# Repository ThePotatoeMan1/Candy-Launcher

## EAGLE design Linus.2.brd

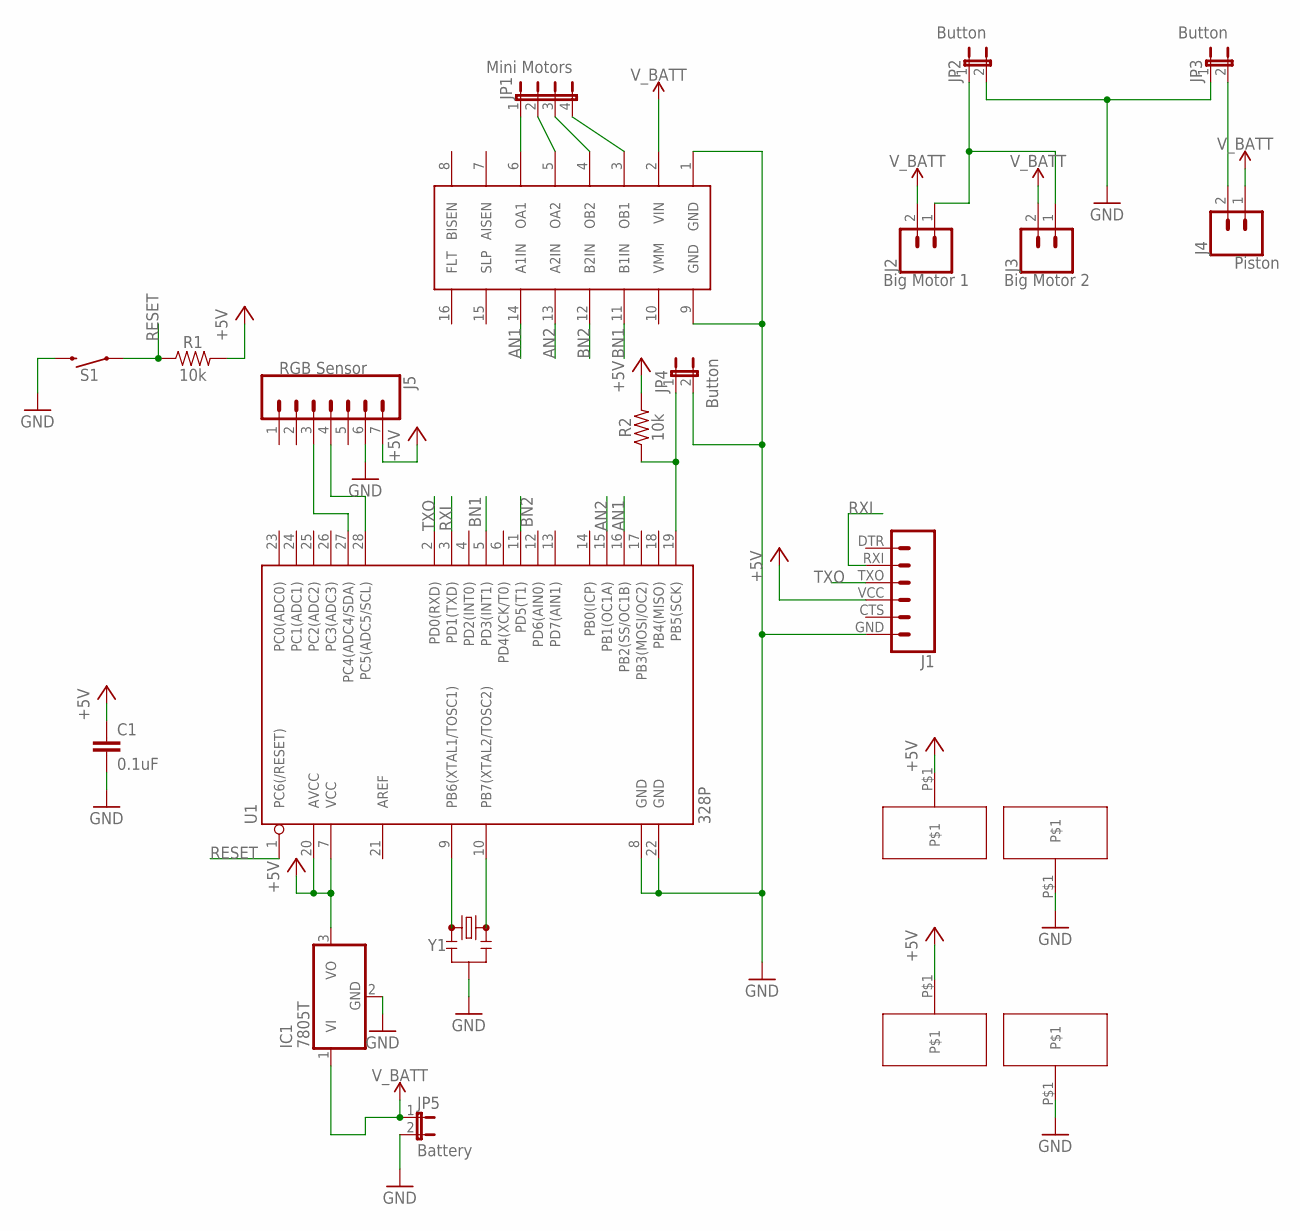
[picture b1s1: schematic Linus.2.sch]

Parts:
C1: 0.1uF; CAP-PTH-SMALL-KIT
IC1: 7805T; TO220H
J1: 6_PIN_SERIAL_CABLEPTH; FTDI_BASIC
J2: Big Motor 1; 1X02
J3: Big Motor 2; 1X02
J4: Piston; 1X02
J5: RGB Sensor; 1X07
JP1: Mini Motors; JP4
JP2, JP3, JP4: Button; JP1
JP5: Battery; JP1
R1, R2: 10k; AXIAL-0.3
S1: MOMENTARY-SWITCH-SPST-PTH-6.0MM; TACTILE_SWITCH_PTH_6.0MM
U1: 328P; DIP28
U$2: MOTOR_DRIVER
U$3, U$4, U$5, U$6: CONN_01
Y1: RESONATORPTH-7.6X3.8; RESONATOR-PTH-7.6X3.8

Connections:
+5V: C1.1, IC1.3 (VO), J1.VCC (4), J5.7, R1.P$2 (2), R2.P$2 (2), U1.7 (VCC), U1.20 (AVCC), U$3.P$1, U$5.P$1
AN1: U1.16 (PB2(SS/OC1B)), U$2.14 (A1IN)
AN2: U1.15 (PB1(OC1A)), U$2.13 (A2IN)
BN1: U1.5 (PD3(INT1)), U$2.11 (B1IN)
BN2: U1.11 (PD5(T1)), U$2.12 (B2IN)
GND: C1.2, IC1.2 (GND), J5.6, JP2.2, JP3.1, JP5.2, S1.3 (2), U$4.P$1, U$6.P$1, Y1.2
unnamed: J5.3, U1.27 (PC4(ADC4/SDA))
unnamed: J5.4, U1.28 (PC5(ADC5/SCL))
unnamed: U1.9 (PB6(XTAL1/TOSC1)), Y1.1
unnamed: U1.10 (PB7(XTAL2/TOSC2)), Y1.3
unnamed: JP1.1, U$2.6 (OA1)
unnamed: JP1.2, U$2.5 (OA2)
unnamed: JP1.3, U$2.4 (OB2)
unnamed: JP1.4, U$2.3 (OB1)
unnamed: J1.GND (6), JP4.2, U1.8 (GND), U1.22 (GND), U$2.1 (GND), U$2.9 (GND)
unnamed: J2.1, J3.1, JP2.1
unnamed: J4.2, JP3.2
unnamed: JP4.1, R2.P$1 (1), U1.19 (PB5(SCK))
RESET: R1.P$1 (1), S1.1, U1.1 (PC6(/RESET))
RXI: J1.RXI (2), U1.3 (PD1(TXD))
TXO: J1.TXO (3), U1.2 (PD0(RXD))
V_BATT: IC1.1 (VI), J2.2, J3.2, J4.1, JP5.1, U$2.2 (VIN)

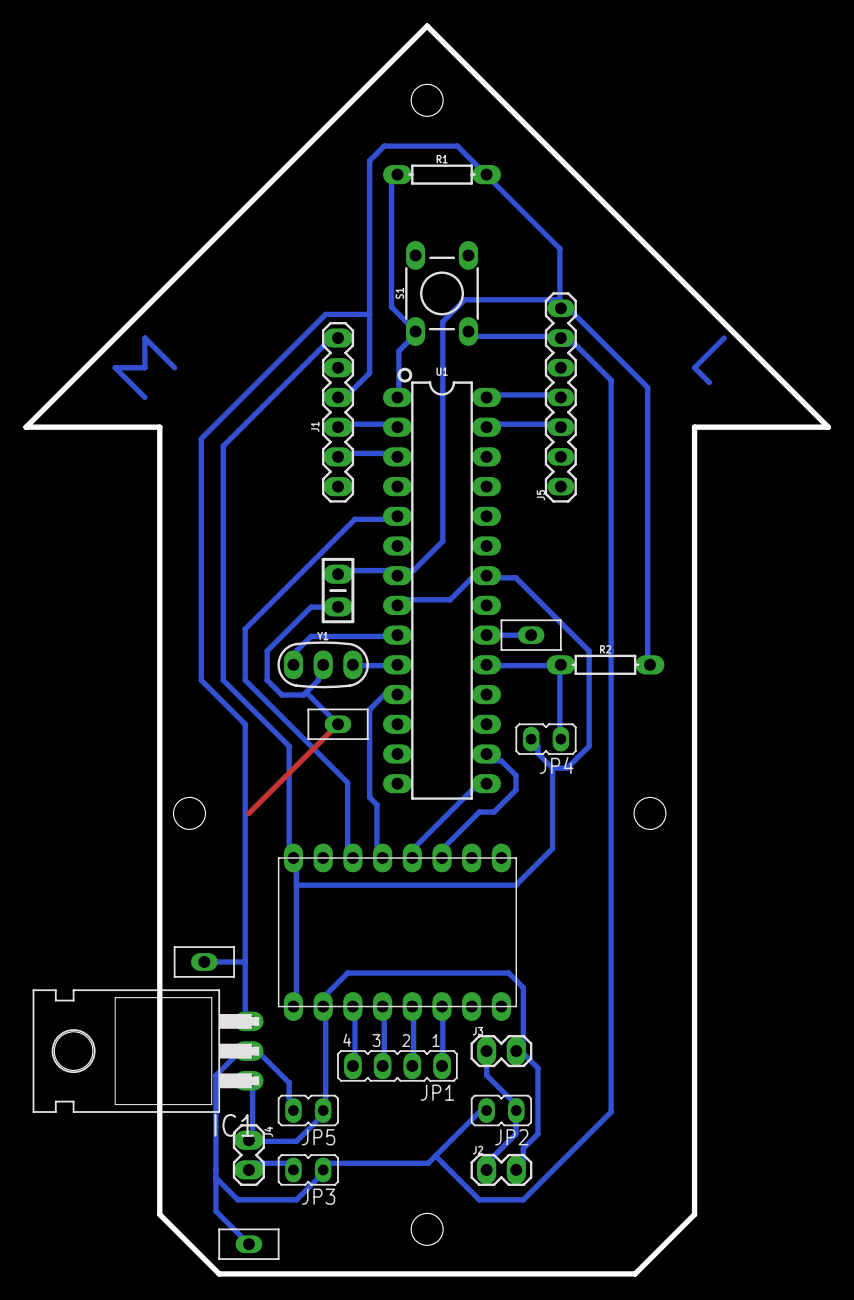
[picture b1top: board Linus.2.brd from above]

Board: 2 copper layers, 68.6 x 106.7 mm, 22 parts (0 on the bottom side), 22 nets.

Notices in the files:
parts and their libraries:
SparkFun-PowerSymbols: Licensing: Creative Commons ShareAlike 4.0 International - https://creativecommons.org/licenses/by-sa/4.0
